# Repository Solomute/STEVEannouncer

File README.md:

If you are here you have probably opened up one of my announce boxes and are trying to fix it.

The buttons and potentiometers are connected to the board via JST PH 2mm headers. You can buy pre-terminated PH cables from many electronics suppliers, including Amazon. JST makes many models of connector, ensure you are buying the PH.

The buttons are SPST NO. I use a Cherry MX mechanical keyboard switch, the top panel cutout is 0.55" square for a Cherry MX or compatible switch to snap into. Many other brands of mechanical keyboard switches are also designed to snap into the same cutout. Simply search the web for "mechanical keyboard switch."

The potentiometers are 10k linear. Do not use a pot with a value other than 10k. Do not use an "audio" or "log" taper pot. The longest-life pots as of the time of this writing use conductive plastic as the resistance element. Avoid carbon. The front panel cutouts for the pots are sized for a standard 6mm diameter shaft. 1/4" diameter shafts should fit too. For knob compatibility get a pot with a 6mm 18T knurled shaft. If you get some other size, or a flatted-D shaft, you're on your own for knobs.

I used a P160KN-0QD15B10K from TT Electronics, but compatibile parts are available from many manufacturers.

My recommendation is that if you are using these boxes in a production environment, you keep a few extra potentiometers and buttons around pre-wired with JSTs. This way, if a pot or button starts dying, you can swap it out in only a couple of minutes. Maybe even during a commercial break!

No audio flows through the buttons or pots. The box will pass audio with a failed switch. A failed pot will cause the headphone to mute, though in practice, the headphone circuit should keep working flawlessly with pots that are degraded well past the point where they would start sounding "scratchy" if audio were passing directly through them.

XLR Input (female) connectors are Neutrik NC3FAH2. XLR Output (male) connectors are Neutrik NC3MAH. 1/4" TRS headphone connectors are Neutrik NRJ6HF. The DC power input is Switchcraft L721RALP.

Neutrik makes many connectors which are electrically and mechanically compatible with the above, and they all should work. For an alternative to the Switchcraft part, you could use a panel-mounted barrel jack and simply run wires off it into the PCB if necessary.

I strongly recommend a *threaded* barrel jack, and power supplies with *threaded* barrel plugs. Being able to lock the power connector is the reason I used a barrel jack instead of a USB plug for DC power.

For more esoteric repairs, consult the schematics. If THAT Corp or Texas Instruments have gone out of business by the time you read this, God help you. Most other parts on the board are generic, but hi-fi audio parts and switching regulators are hard to multi-source, unfortunately.

Design files for the enclosure are also included - You might be able to get away with 3D printing it, but I recommend using SendCutSend to have it cut and bent out of sheet metal with PCB standoffs inserted. Use 6mm M3x0.5 standoffs. OSHCut is talking about adding hardware insertion to their services, so they might be an option as well by the time you read this.

Good luck!

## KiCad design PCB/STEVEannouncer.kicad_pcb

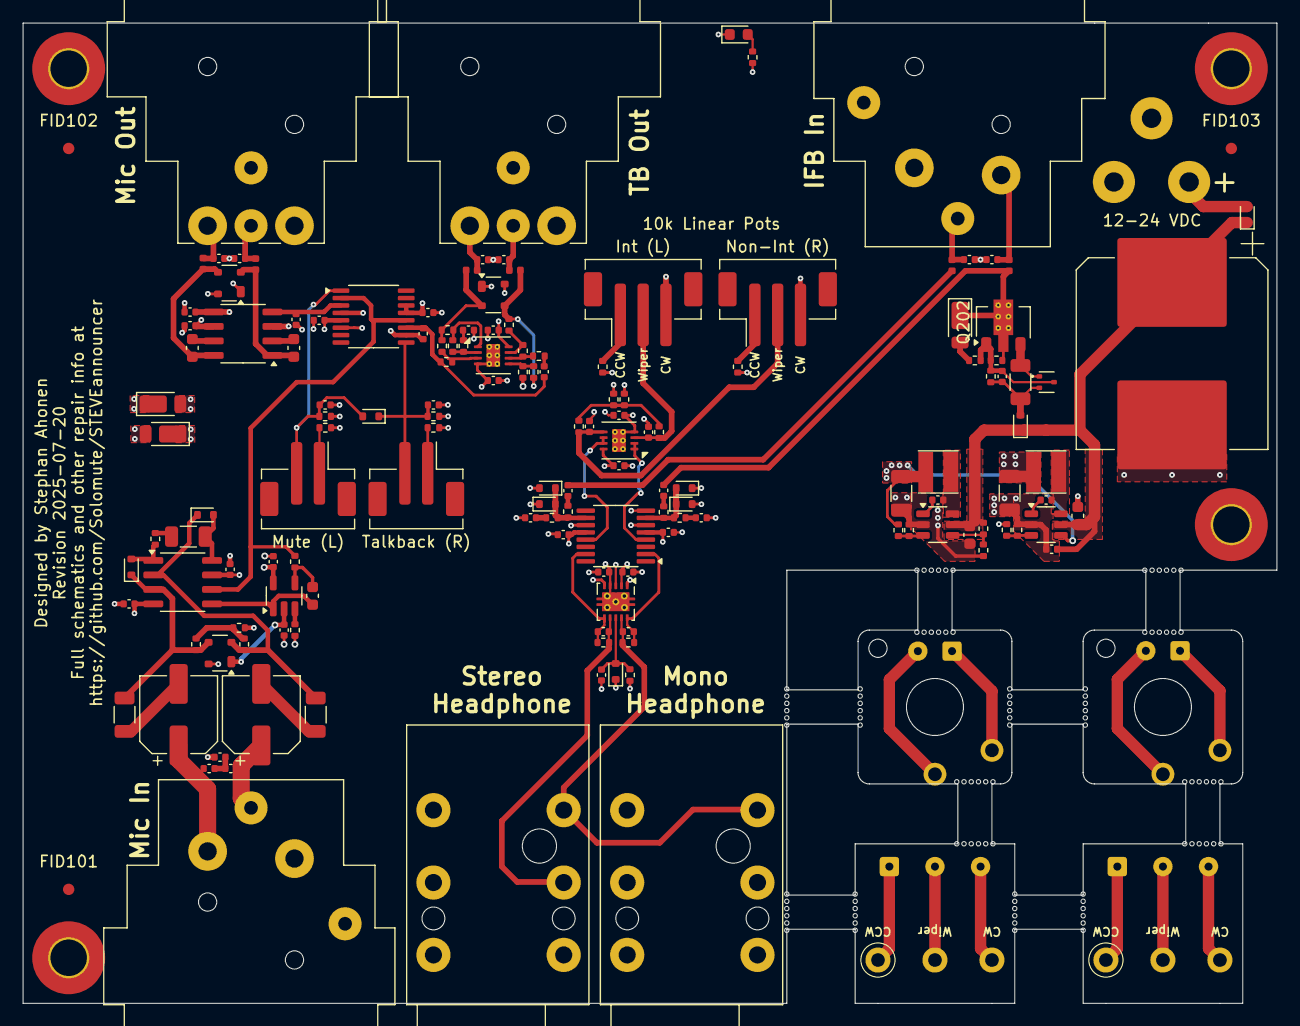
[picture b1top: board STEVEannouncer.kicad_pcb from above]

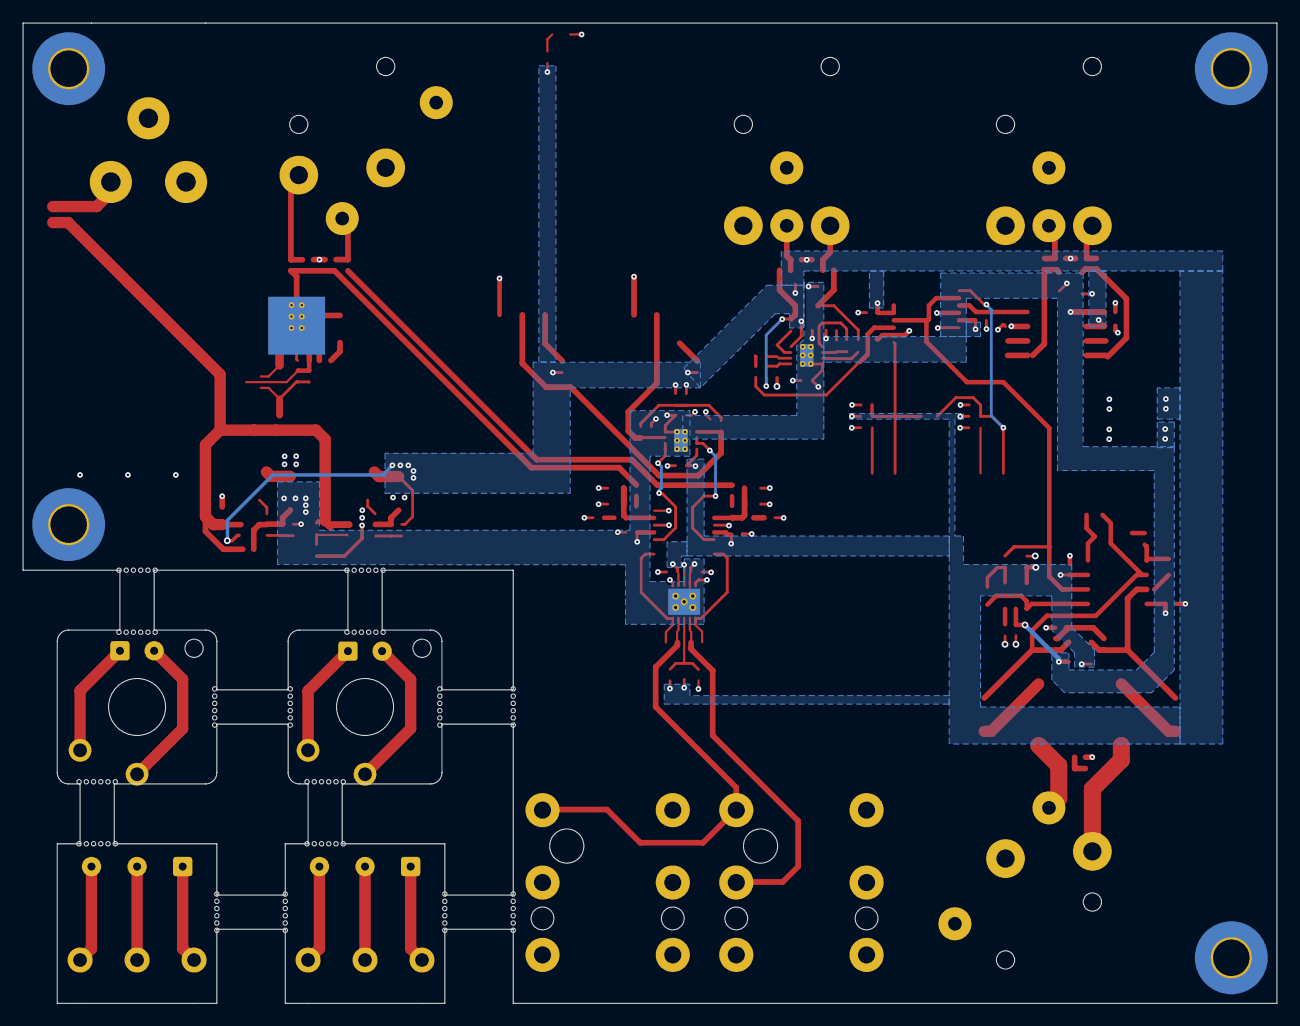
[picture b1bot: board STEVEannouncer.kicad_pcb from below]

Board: 4 copper layers, 110.0 x 86.0 mm, 180 parts (2 on the bottom side), 88 nets.

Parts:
C201, C401, C402, C409: 1u/50V; C_0402_1005Metric
C202: 1000u; CP_Elec_16x17.5
C203, C204: 2.2u; C_0603_1608Metric
C205, C206, C209, C301, C308, C309, C310, C311, C312, C313, C314, C315, C322, C323, C324, C325, C326, C405, C406, C410, C411, C412, C413, C414, C415: 100n; C_0402_1005Metric
C207, C208: 22u; C_1206_3216Metric
C302, C318, C319, C320, C321, C403, C404, C407, C408, C416, C417: 100p; C_0402_1005Metric
C303, C304, C328, C329: 470p; C_0402_1005Metric
C305, C306: 22u; CP_Elec_6.3x7.7
C307: 100u; C_1206_3216Metric
C316, C317, C327: 10u; C_0603_1608Metric
D201, D302, D303: DFLZ5V6; D_PowerDI-123
D202, D203, D306: D_Schottky; D_SOD-523
D204: LED; LED_0603_1608Metric
D301, D307, D308: BAS3007; SOT-143
D304, D305, D401, D402, D403, D404, D405: BAS716; D_SOD-523
FB301, FB302, FB303, FB304, FB401, FB402: FerriteBead; L_0402_1005Metric
FID101, FID102, FID103: Fiducial; Fiducial_1mm_Mask3mm
H101, H102, H103, H104: MountingHole; MountingHole_3.2mm_M3_Pad_TopBottom
H105, H106, H107, H108, H109, H110, H111, H112, H113, H114, H115, H116, H117, H118, H119, H120: Mousebites
J201: Barrel_Jack_Switch; Barrel Jack
J301, J401: NC3FAH2
J302, J305: Conn_01x02; SolderWire-0.15sqmm_1x02_P4mm_D0.5mm_OD1.5mm
J303, J304: Conn_01x02; JST_PH_B2B-PH-SM4-TB_1x02-1MP_P2.00mm_Vertical
J306, J307: NC3MAH
J402, J404: Conn_01x03; SolderWire-0.15sqmm_1x03_P4mm_D0.5mm_OD1.5mm
J403, J405: Conn_01x03; JST_PH_B3B-PH-SM4-TB_1x03-1MP_P2.00mm_Vertical
J406, J407: NRJ6HF
L201, L202: 18u; Inductor 3012
Q201: BC847; SOT-523
Q202: BCV49; SOT-89-3
R201, R413: 1Meg; R_0402_1005Metric
R202, R309, R310, R405, R406: 330k; R_0402_1005Metric
R203, R205, R206, R305, R307, R308, R311, R312, R313, R314, R401, R402, R411, R412: 20k; R_0402_1005Metric
R204, R301, R302: 10; R_1206_3216Metric
R207, R208, R210, R407, R408, R409: 80.6k; R_0402_1005Metric
R209, R303, R304, R315, R316, R317, R318: 1k; R_0402_1005Metric
R211, R321, R322, R410: 10k; R_0402_1005Metric
R306, R319, R320: 100; R_0402_1005Metric
R403, R404: 6.8k; R_0402_1005Metric
RV401, RV402: 10k; Pot
SW301, SW302: SW_SPST; SW_choc_v1_1u
U201, U202: LV3842; SOT-23-6
U301: TMUX6236; TSSOP-16_4.4x5mm_P0.65mm
U302, U402: OPA1678; WSON-8-1EP_3x3mm_P0.5mm_EP1.2x2mm_ThermalVias
U303: THAT1512; SO-8_3.9x4.9mm_P1.27mm
U304: THAT1646; SO-8_3.9x4.9mm_P1.27mm
U305: OPA202; SOT-23-5
U401: THAT2162; QSOP-16_3.9x4.9mm_P0.635mm
U403: OPA1622

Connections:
+5V: C207.1, C308.2, C310.1, C314.2, C322.1, C326.2, C411.1, C412.1, C415.1, D301.4 (+), D302.1 (K), D307.4 (+), D308.4 (+), D405.1 (K), L201.2, R207.2, R209.1, R309.2, R310.2, R407.1, R408.1, R409.1, R413.2, U202.4 (EN), U301.13 (VCC), U301.14 (EN), U302.8 (V+), U303.7 (V+), U304.6 (V+), U305.5 (V+), U401.12 (V+), U402.8 (V+), U403.2 (V+)
-5V: C208.2, C209.1, C301.1, C309.2, C311.1, C315.2, C325.2, C410.2, C413.2, C414.2, D301.1 (-), D303.2 (A), D307.1 (-), D308.1 (-), R206.2, U202.2 (GND), U301.5 (VSS), U302.4 (V-), U302.9 (Pad), U303.4 (V-), U304.5 (V-), U305.2 (V-), U401.5 (V-), U402.4 (V-), U402.9 (Pad), U403.4 (V-), U403.11 (V-)
/IFB Path/HP_L: C407.2, J406.T, J407.T, R411.2, U403.9
/IFB Path/HP_R: C408.2, J406.R, R412.2, U403.7
/IFB Path/IFB_Pin3: C402.1, FB402.2
/IFB Path/VCAL_E-: U401.4 (E-), U402.1, U402.2 (-)
/IFB Path/VCAR_E-: U401.13 (E-), U402.6 (-), U402.7
/IFB Path/VCA_INL: D401.2 (A), D403.1 (K), R401.2, R403.1, U401.7 (IN)
/IFB Path/VCA_INR: D402.2 (A), D404.1 (K), R402.2, R404.1, U401.10 (IN)
/IFB Path/VCA_OUTL: C407.1, R411.1, U401.2 (OUT), U403.10 (-)
/IFB Path/VCA_OUTR: C408.1, R412.1, U401.15 (OUT), U403.6 (-)
/Mic Path/Mic2: C303.1, C305.1, J301.2
/Mic Path/Mic3: C304.2, C306.1, J301.3
/Mic Path/MicOut: C328.1, U301.3 (D), U304.4 (IN)
/Mic Path/MicOut2: C318.1, FB301.2, J307.2
/Mic Path/MicOut3: C319.2, FB302.2, J307.3
/Mic Path/MicOut+: C316.2, D307.3, FB301.1, U304.8 (OUT+)
/Mic Path/MicOut-: C317.2, D307.2, FB302.1, U304.1 (OUT-)
/Mic Path/Micpre+: D301.3, D304.1 (K), R301.1, R303.1, U303.3 (+In)
/Mic Path/Micpre-: D301.2, D305.1 (K), R302.1, R304.2, U303.2 (-In)
/Mic Path/MicpreOut: R321.1, U301.2 (SA), U301.12 (SB), U303.6 (Out)
/Mic Path/MuteSel: C324.2, D306.2 (A), J304.2, R309.1, U301.1 (SEL)
/Mic Path/RG1: D304.2 (A), R306.2, U303.1 (Rg1)
/Mic Path/RG2: C307.2, D305.2 (A), U303.8 (Rg2)
/Mic Path/TBOut: C313.2, C329.1, R311.1, U301.11 (D)
/Mic Path/TBSel: C323.2, D306.1 (K), J303.2, R310.1, U301.9 (SEL)
/Mic Path/TB_OUT2: C320.1, FB303.2, J306.2
/Mic Path/TB_OUT3: C321.2, FB304.2, J306.3
/Power/Darl_B: C201.1, Q201.3 (C), Q202.1 (B), R201.2, R202.1, R203.2
/Power/Darl_E: Q201.1 (B), Q202.3 (E), R204.1
/Power/Pin2_Bulk: C201.2, D202.2 (A), Q201.2 (E), R202.2, R204.2
/Power/vbulk: C202.1, C203.1, C204.1, C209.2, D202.1 (K), D203.1 (K), R210.2, U201.5 (VIN), U202.5 (VIN)
GND: C202.2, C203.2, C204.2, C207.2, C208.1, C301.2, C302.1, C308.1, C309.1, C310.2, C311.2, C312.1, C314.1, C315.1, C318.2, C319.1, C320.2, C321.1, C322.2, C323.1, C324.1, C325.1, C326.1, C328.2, C329.2, C403.2, C404.2, C405.2, C406.2, C409.1, C410.1, C411.2, C412.2, C413.1, C414.1, C415.2, C416.2, C417.1, D204.1 (K), D302.2 (A), D303.1 (K), D401.1 (K), D402.1 (K), D403.2 (A), D404.2 (A), H101.1, H102.1, H103.1, H104.1, J201.2, J201.3, J301.1, J301.G, J306.1, J306.G, J307.1, J307.G, J401.1, J401.G, J403.3, J405.3, J406.S, J406.SN, J407.S, J407.SN, L202.2, R205.2, R208.2, R211.1, R305.2, R307.2, R308.2, R314.1, R322.2, R410.1, U201.2 (GND), U301.4 (SB), U301.6 (GND), U301.10 (SA), U304.3 (GND), U401.6 (E+), U401.8 (GND), U401.11 (E+), U403.1 (+), U403.3 (GND), U403.5 (+)
IFB_PIN2: C401.1, D201.1 (K), FB401.2, Q202.2 (C), R201.1
unnamed: C302.2, C303.2, C304.1
unnamed: C305.2, R301.2
unnamed: C306.2, R302.2
unnamed: C307.1, R306.1
unnamed: C312.2, R313.1
unnamed: C313.1, R312.1
unnamed: C401.2, R401.1
unnamed: C402.2, R402.1
unnamed: C403.1, R403.2
unnamed: C404.1, R404.2
unnamed: C416.1, FB401.1, J401.2
unnamed: C417.2, FB402.1, J401.3
unnamed: D201.2 (A), R203.1
unnamed: D203.2 (A), J201.1
unnamed: D204.2 (A), R209.2
unnamed: D308.2, FB303.1, R315.1, R319.2
unnamed: D308.3, FB304.1, R318.1, R320.2
unnamed: C409.2, D405.2 (A), R413.1, U403.8 (EN)
unnamed: J302.1, SW301.1 (A)
unnamed: J302.2, SW301.2 (B)
unnamed: J303.1, R307.1
unnamed: J304.1, R308.1
unnamed: J305.1, SW302.1 (A)
unnamed: J305.2, SW302.2 (B)
unnamed: J402.1, RV401.1
unnamed: J402.2, RV401.2
unnamed: J402.3, RV401.3
unnamed: J403.1, R407.2
unnamed: C406.1, J403.2, R406.2, U402.5 (+)
unnamed: J404.1, RV402.1
unnamed: J404.2, RV402.2
unnamed: J404.3, RV402.3
unnamed: J405.1, R408.2
unnamed: C405.1, J405.2, R405.1, U402.3 (+)
unnamed: R303.2, R304.1, R305.1
unnamed: R316.1, R319.1, U302.1
unnamed: R317.1, R320.1, U302.7
unnamed: R405.2, R406.1, R409.2, R410.2
unnamed: C205.1, U201.1 (Boot)
unnamed: R210.1, R211.2, U201.4 (EN)
unnamed: R205.1, R207.1, U201.3 (FB)
unnamed: C205.2, L201.1, U201.6 (SW)
unnamed: C206.1, U202.1 (Boot)
unnamed: R206.1, R208.1, U202.3 (FB)
unnamed: C206.2, L202.1, U202.6 (SW)
unnamed: R311.2, R315.2, U302.3 (+)
unnamed: R313.2, R316.2, U302.2 (-)
unnamed: R314.2, R318.2, U302.5 (+)
unnamed: R312.2, R317.2, U302.6 (-)
unnamed: C327.2, U303.5 (Ref), U305.1
unnamed: C316.1, U304.7 (SNS+)
unnamed: C317.1, U304.2 (SNS-)
unnamed: R322.1, U305.3 (+)
unnamed: C327.1, R321.2, U305.4 (-)

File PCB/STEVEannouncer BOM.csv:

"Reference","Qty","Value","Footprint","Mouser Part Number"
"U301","1","TMUX6236","Package_SO:TSSOP-16_4.4x5mm_P0.65mm","595-TMUX6236PWR"
"U401","1","THAT2162","Package_SO:QSOP-16_3.9x4.9mm_P0.635mm","887-2162Q16-U"
"U304","1","THAT1646","Package_SO:SO-8_3.9x4.9mm_P1.27mm","887-1646S08-U"
"U303","1","THAT1512","Package_SO:SO-8_3.9x4.9mm_P1.27mm","887-1512S08-U"
"SW301,SW302","2","SW_SPST","STEVEannouncer:SW_choc_v1_1u","540-MX1A-C1NN"
"B401,B402","2","Plastic Nut","","550-1005"
"U302,U402","2","OPA1678","STEVEannouncer:WSON-8-1EP_3x3mm_P0.5mm_EP1.2x2mm_ThermalVias","595-OPA1678IDRGR"
"U403","1","OPA1622","STEVEannouncer:OPA1622","595-OPA1622IDRCT"
"J406,J407","2","NRJ6HF","STEVEannouncer:NRJ6HF","550-20311"
"J301,J401","2","NC3FAH2","STEVEannouncer:NC3FAH2",""
"J306,J307","2","NC3MAH","STEVEannouncer:NC3MAH",""
"U201,U202","2","LV3842","STEVEannouncer:SOT-23-6","595-LV3842XDBVR"
"D204","1","LED","LED_SMD:LED_0603_1608Metric",""
"FB301,FB302,FB303,FB304,FB401,FB402","6","FerriteBead","Inductor_SMD:L_0402_1005Metric","673-BBSY100505700Y00"
"D201,D302,D303","3","DFLZ5V6","Diode_SMD:D_PowerDI-123","621-DFLZ5V6-7"
"D202,D203,D306","3","D_Schottky","Diode_SMD:D_SOD-523","755-RB510SM-40T2R"
"J402,J403,J404,J405","4","Conn_01x03","Connector_JST:JST_PH_B3B-PH-SM4-TB_1x03-1MP_P2.00mm_Vertical","306-B3BPHSM4TBLFSN"
"J302,J303,J304,J305","4","Conn_01x02","Connector_JST:JST_PH_B2B-PH-SM4-TB_1x02-1MP_P2.00mm_Vertical","306-B2BPHSM4TBLFSN"
"Q202","1","BCV49","Package_TO_SOT_SMD:SOT-89-3","771-BCV49135"
"Q201","1","BC847","Package_TO_SOT_SMD:SOT-523","621-BC847CT-7-F"
"D301,D307,D308","3","BAS3007ARPPE6327HTSA1","Package_TO_SOT_SMD:SOT-143","726-BAS3007A-RPPE6"
"D304,D305,D401,D402,D403,D404,D405","7","BAS716","Diode_SMD:D_SOD-523","771-BAS716-T/R"
"J201","1","Barrel_Jack_Switch","STEVEannouncer:Barrel Jack","502-L721RALP"
"C201,C401,C402,C409","4","1u/50V","Capacitor_SMD:C_0402_1005Metric","81-GRM155R61H105KE5D"
"R202,R309,R310,R405,R406","5","330k","Resistor_SMD:R_0402_1005Metric",""
"R207,R208,R407,R408,R409","5","80.6k","Resistor_SMD:R_0402_1005Metric",""
"R203,R205,R206,R305,R307,R308,R311,R312,R313,R314,R401,R402,R411,R412","14","20k","Resistor_SMD:R_0402_1005Metric",""
"RV401,RV402","2","10k","STEVEannouncer:Pot","858-P160KN0QD15B10K"
"R410","1","10k","Resistor_SMD:R_0402_1005Metric",""
"R403,R404","2","6.8k","Resistor_SMD:R_0402_1005Metric",""
"R209,R303,R304,R315,R316,R317,R318","7","1k","Resistor_SMD:R_0402_1005Metric",""
"R306","1","270","Resistor_SMD:R_0402_1005Metric",""
"R319,R320","2","100","Resistor_SMD:R_0402_1005Metric",""
"R204,R301,R302","3","10","Resistor_SMD:R_1206_3216Metric",""
"R201,R413","2","1Meg","Resistor_SMD:R_0402_1005Metric",""
"C202","1","1000u","Capacitor_SMD:CP_Elec_16x17.5","667-EEV-FK1H102M"
"C307","1","100u","Capacitor_SMD:C_1206_3216Metric","81-GRM31CR60J107KE8L"
"C305,C306","2","22u","Capacitor_SMD:CP_Elec_6.3x7.7","647-UCD1J220MCL1GS"
"C207,C208","2","22u","Capacitor_SMD:C_1206_3216Metric","791-1206X226K100CT"
"L201,L202","2","18u","STEVEannouncer:Inductor 3012","652-SRN3015BTA-180M"
"C316,C317","2","10u","Capacitor_SMD:C_0603_1608Metric","187-CL10A106KP8NNWC"
"C203,C204","2","2.2u","Capacitor_SMD:C_0603_1608Metric","81-GRT188R61H225KE3D"
"C205,C206,C209,C301,C308,C309,C310,C311,C312,C313,C314,C315,C322,C323,C324,C405,C406,C410,C411,C412,C413,C414,C415","23","100n","Capacitor_SMD:C_0402_1005Metric","81-GRM155R62A104KE4D"
"C303,C304","2","470p","Capacitor_SMD:C_0402_1005Metric",""
"C302,C318,C319,C320,C321,C403,C404,C407,C408,C416,C417","11","100p","Capacitor_SMD:C_0402_1005Metric",""

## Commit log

2025-06-20 Wooooooo
2025-06-20 lalalalala
2025-06-24 progress
2025-06-28 Moar Progress
2025-06-29 Even more more progress
2025-06-29 Yeet
2025-06-30 I think I can fab this????
2025-07-01 There, I ordered it
2025-07-04 Enclosure files
2025-07-20 revisionnnnn
2025-07-20 Rev 2025-07-20
2025-07-20 Tidying up
2025-07-20 moar cleaning
2025-07-20 asdf
2025-07-21 How did those footprints lose their solder mask?????
